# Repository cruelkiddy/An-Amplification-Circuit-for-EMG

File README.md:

# An-Amplification-Circuit-for-EMG
An amplification circuit for EMG. It adopts the classic Driven Right Leg (DRL) circuit scheme. It achieves a 64.3dB SNR and has a compact size of 66.2 mm×24.4 mm. The schematic and layout is shown below, and they are created with KiCAD. 

## Schematic
[here](KiCADSchem.pdf)

## Layout
[here](KiCADLayout.pdf)

## A typical waveform produced by the circuit
[here](contraction.pdf)

## Full list of materials

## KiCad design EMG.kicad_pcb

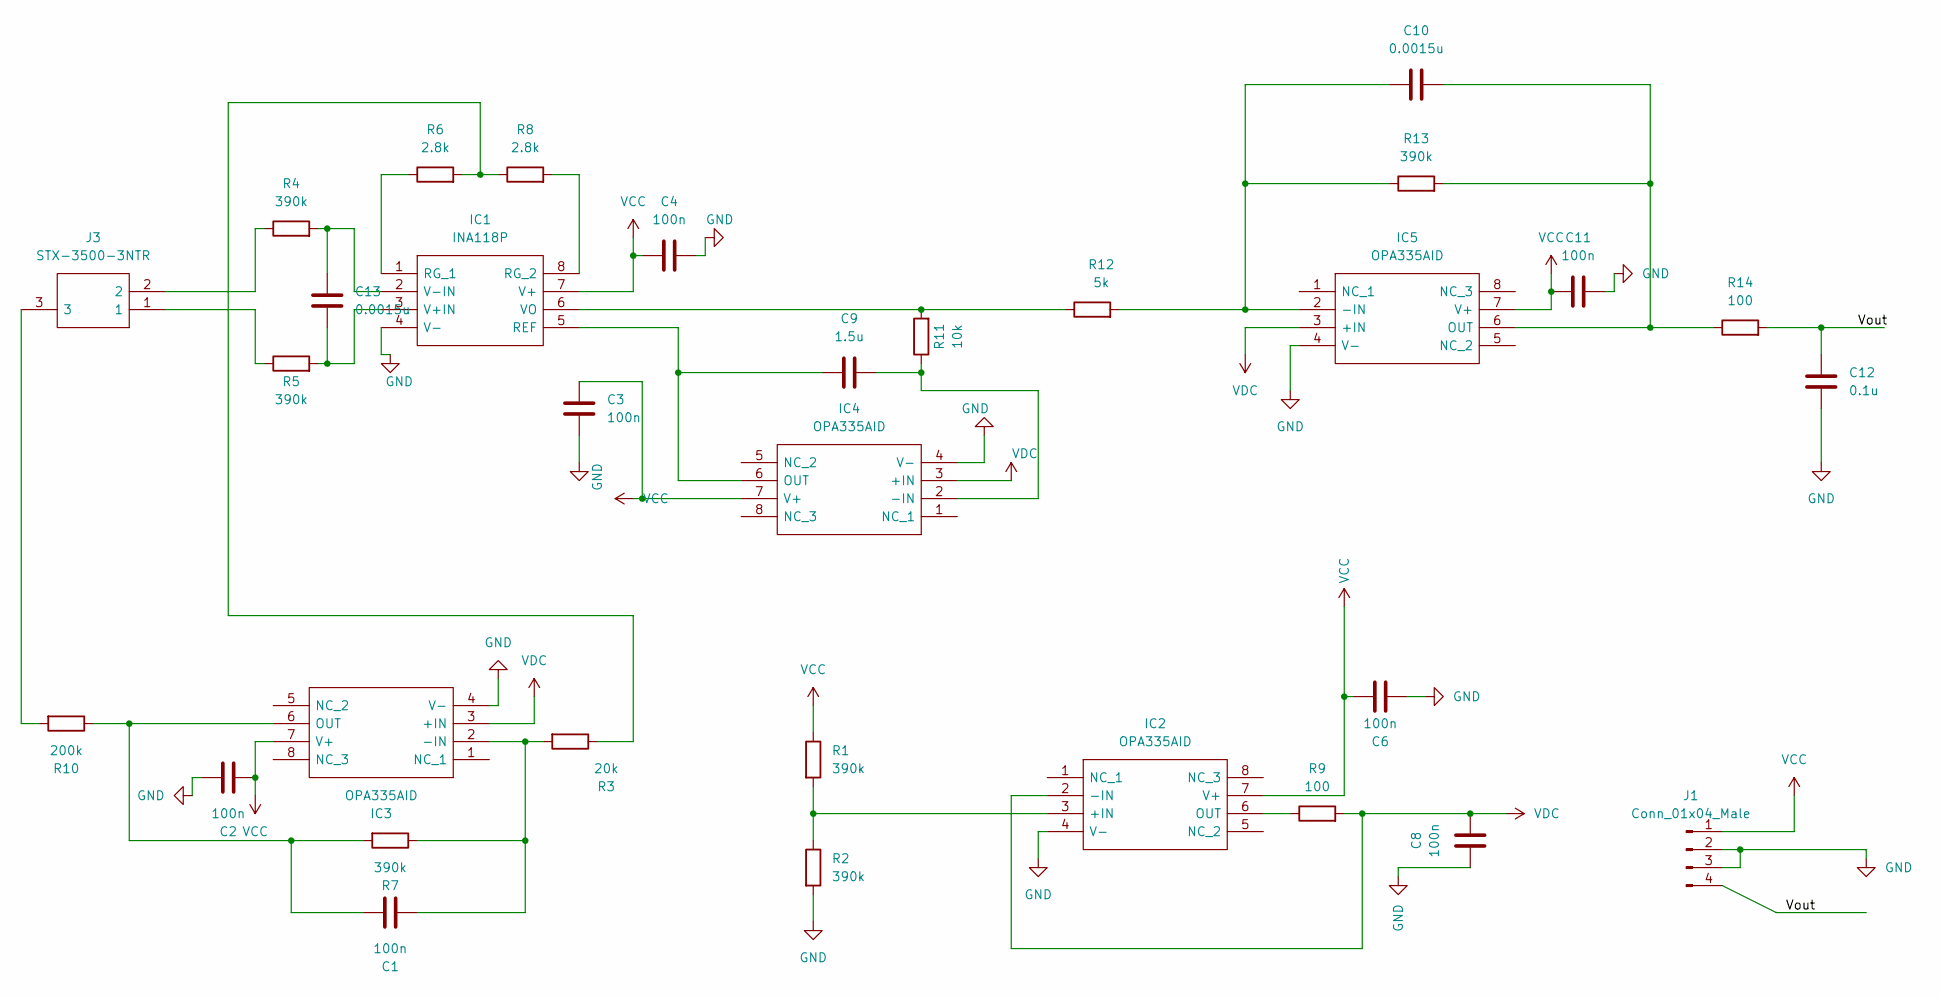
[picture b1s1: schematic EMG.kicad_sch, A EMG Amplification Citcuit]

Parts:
C1, C2, C3, C4, C6, C8, C11: 100n; C0805
C9: 1.5u; C0805
C10, C13: 0.0015u; C0805
C12: 0.1u; C0805
IC1: INA118P; DIP794W53P254L959H508Q8N; Mouser Part Number 595-INA118P
IC2, IC3, IC4, IC5: OPA335AID; SOIC127P600X175-8N; Mouser Part Number 595-OPA335AID
J1: Conn_01x04_Male; FanPinHeader_1x04_P2.54mm_Vertical
J3: STX-3500-3NTR; STX35003NTR; Mouser Part Number 806-STX-3500-3NTR
R1, R2, R4, R5, R7, R13: 390k; C0805
R3: 20k; C0805
R6, R8: 2.8k; C0603
R9, R14: 100; C0805
R10: 200k; C0805
R11: 10k; C0805
R12: 5k; CAPC3216X94N

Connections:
/Vout: C12.2, J1.4, R14.2
GND: C2.2, C3.2, C4.2, C6.2, C8.1, C11.2, C12.1, IC1.4 (V-), IC2.4 (V-), IC3.4 (V-), IC4.4 (V-), IC5.4 (V-), J1.2, J1.3, R2.2
unnamed: C1.1, IC3.2 (-IN), R3.2, R7.1
unnamed: C1.2, IC3.6 (OUT), R7.2, R10.1
unnamed: C9.1, IC1.5 (REF), IC4.6 (OUT)
unnamed: C9.2, IC4.2 (-IN), R11.1
unnamed: C10.1, IC5.2 (-IN), R12.2, R13.1
unnamed: C10.2, IC5.6 (OUT), R13.2, R14.1
unnamed: C13.1, IC1.3 (V+IN), R5.2
unnamed: C13.2, IC1.2 (V-IN), R4.2
unnamed: IC1.1 (RG_1), R6.1
unnamed: IC1.6 (VO), R11.2, R12.1
unnamed: IC1.8 (RG_2), R8.2
unnamed: IC2.3 (+IN), R1.2, R2.1
unnamed: IC2.6 (OUT), R9.1
unnamed: J3.1, R5.1
unnamed: J3.2, R4.1
unnamed: J3.3, R10.2
unnamed: R3.1, R6.2, R8.1
VCC: C2.1, C3.1, C4.1, C6.1, C11.1, IC1.7 (V+), IC2.7 (V+), IC3.7 (V+), IC4.7 (V+), IC5.7 (V+), J1.1, R1.1
VDC: C8.2, IC2.2 (-IN), IC3.3 (+IN), IC4.3 (+IN), IC5.3 (+IN), R9.2

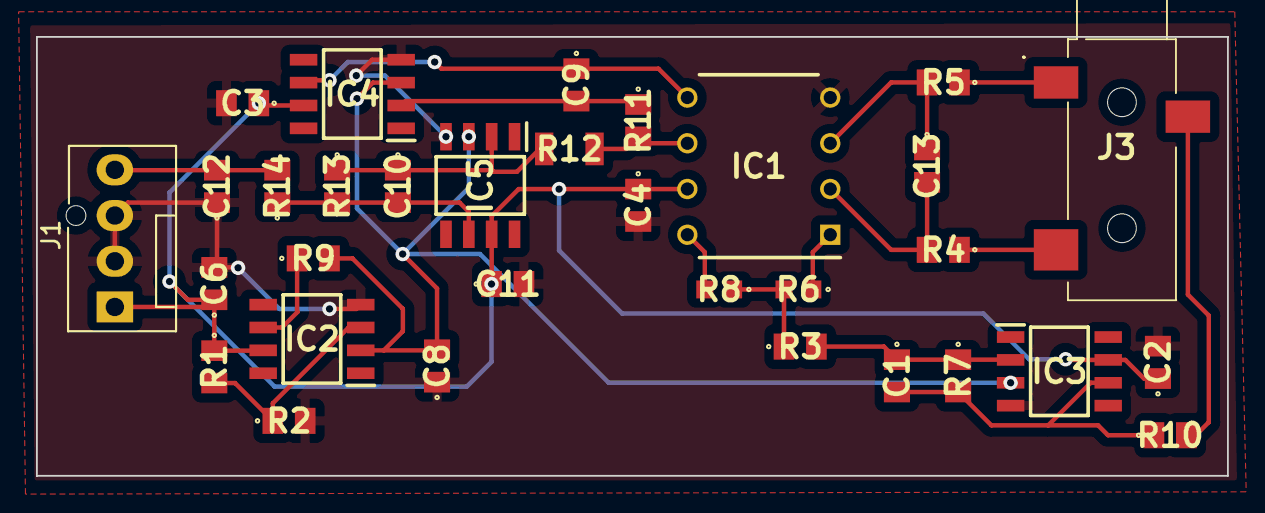
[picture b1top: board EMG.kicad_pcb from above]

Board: 2 copper layers, 66.2 x 24.4 mm, 32 parts (0 on the bottom side), 21 nets.

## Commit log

2022-08-23 Create LICENSE
